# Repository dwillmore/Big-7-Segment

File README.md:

# Big-7-Segment
Replacement for a 3542BS 4 digit + colon 7 segment display module using LED filaments

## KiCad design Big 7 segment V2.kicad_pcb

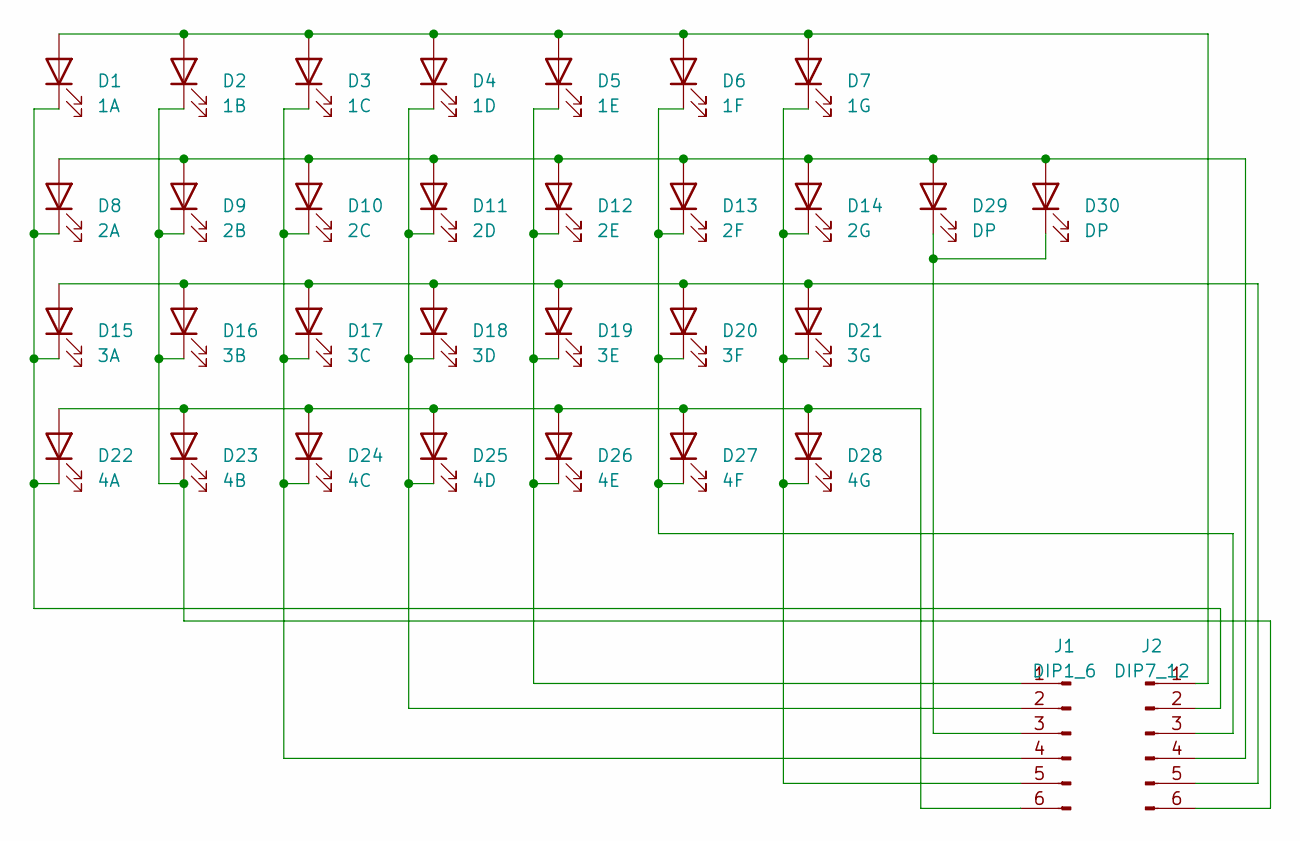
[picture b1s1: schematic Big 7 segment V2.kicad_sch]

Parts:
D1: 1A; 32mm LED
D2: 1B; 32mm LED
D3: 1C; 32mm LED
D4: 1D; 32mm LED
D5: 1E; 32mm LED
D6: 1F; 32mm LED
D7: 1G; 32mm LED
D8: 2A; 32mm LED
D9: 2B; 32mm LED
D10: 2C; 32mm LED
D11: 2D; 32mm LED
D12: 2E; 32mm LED
D13: 2F; 32mm LED
D14: 2G; 32mm LED
D15: 3A; 32mm LED
D16: 3B; 32mm LED
D17: 3C; 32mm LED
D18: 3D; 32mm LED
D19: 3E; 32mm LED
D20: 3F; 32mm LED
D21: 3G; 32mm LED
D22: 4A; 32mm LED
D23: 4B; 32mm LED
D24: 4C; 32mm LED
D25: 4D; 32mm LED
D26: 4E; 32mm LED
D27: 4F; 32mm LED
D28: 4G; 32mm LED
D29, D30: DP; LED_D5.0mm
J1: DIP1_6; PinHeader_1x06_P2.54mm_Vertical_SMD_Pin1Left
J2: DIP7_12; PinHeader_1x06_P2.54mm_Vertical_SMD_Pin1Right

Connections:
unnamed: D1.2 (A), D2.2 (A), D3.2 (A), D4.2 (A), D5.2 (A), D6.2 (A), D7.2 (A), J2.1
unnamed: D1.1 (K), D8.1 (K), D15.1 (K), D22.1 (K), J2.2
unnamed: D8.2 (A), D9.2 (A), D10.2 (A), D11.2 (A), D12.2 (A), D13.2 (A), D14.2 (A), D29.2 (A), D30.2 (A), J2.4
unnamed: D3.1 (K), D10.1 (K), D17.1 (K), D24.1 (K), J1.4
unnamed: D4.1 (K), D11.1 (K), D18.1 (K), D25.1 (K), J1.2
unnamed: D5.1 (K), D12.1 (K), D19.1 (K), D26.1 (K), J1.1
unnamed: D6.1 (K), D13.1 (K), D20.1 (K), D27.1 (K), J2.3
unnamed: D7.1 (K), D14.1 (K), D21.1 (K), D28.1 (K), J1.5
unnamed: D15.2 (A), D16.2 (A), D17.2 (A), D18.2 (A), D19.2 (A), D20.2 (A), D21.2 (A), J2.5
unnamed: D2.1 (K), D9.1 (K), D16.1 (K), D23.1 (K), J2.6
unnamed: D22.2 (A), D23.2 (A), D24.2 (A), D25.2 (A), D26.2 (A), D27.2 (A), D28.2 (A), J1.6
unnamed: D29.1 (K), D30.1 (K), J1.3

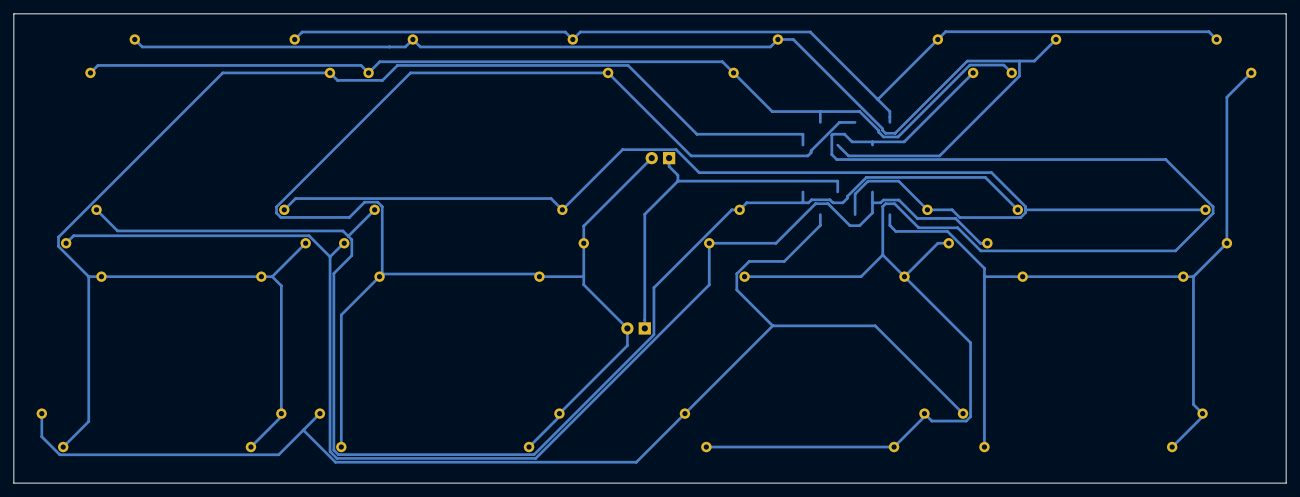
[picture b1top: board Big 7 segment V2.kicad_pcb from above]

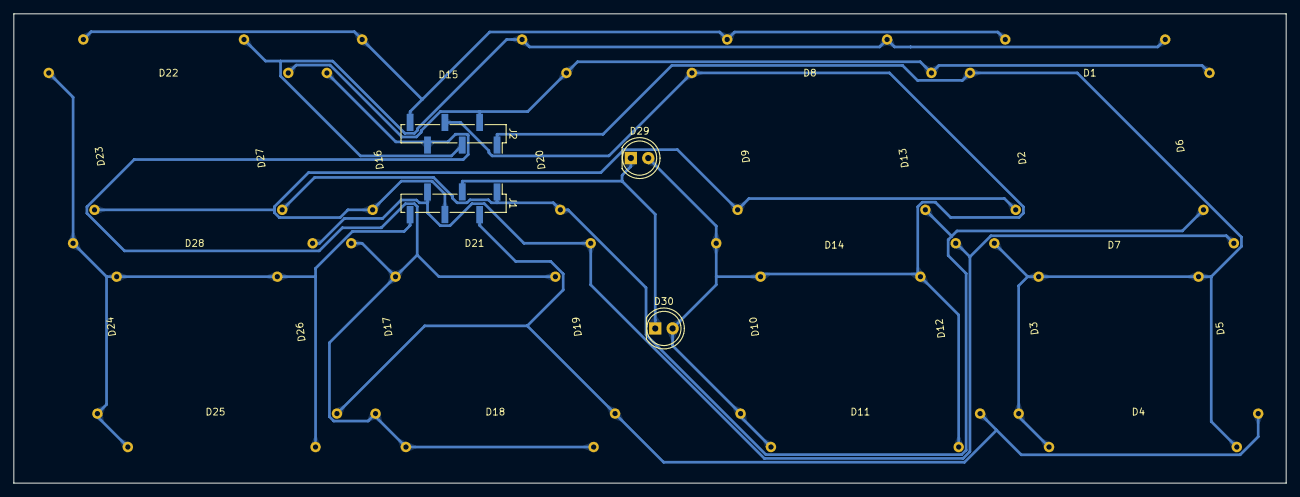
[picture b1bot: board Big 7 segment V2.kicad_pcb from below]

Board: 2 copper layers, 185.9 x 68.6 mm, 32 parts (4 on the bottom side), 12 nets.

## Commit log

2024-08-18 Initial commit of V2 with 0.4" header
    Fixed schematic errors on B segments, changed trace width to 0.4mm and altered header spacing/alignment to match the display module
2024-08-18 Production files targeted for JLCPCB
    Gerbers, drill, map files for fabrication at JLCPCB
